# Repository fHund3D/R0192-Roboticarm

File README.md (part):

# Roboticarm-R0192

Der **R0192** ist ein 6-Achsen-Roboterarm, der auf einem hybriden System aus SteadyWin- und RobStride-Aktuatoren basiert. Dieses Repository enthält das vollständige ROS 2 Jazzy-Ökosystem für die CAN-Bus-Kommunikation, die Hardware-Abstraktion, die Bahnplanung via MoveIt 2 sowie ein Arduino-basiertes Hall-Sensor-Homing.

Die gesamte Steuerungslogik (MoveIt 2, ros2_control, CAN-Treiber) läuft auf einem **Raspberry Pi 5**. Eine zentrale **Betriebszustands-Maschine** (`robot_state_manager`) koordiniert Motor-Enable, Jogging, MoveIt-Ausführung, Homing und Notaus als sich gegenseitig ausschließende Zustände. Bedient wird der Arm über ein **RViz-Jog-Panel**, das gezielt zu einem Teach-Pendant-Ersatz ausgebaut wird (später ggf. durch ein echtes Hardware-Teach-Pendant ersetzbar); ein **Web-Interface** (`r0192_remote`) bleibt eine optionale Zukunftsoption. Foxglove Studio spielt nur eine kleine Rolle zum Debuggen. **Alle sechs Aktuatoren sind inzwischen beschafft und montagebereit**; softwareseitig sind die GDS68- und RS05-Antriebsstränge an je einer Achse verifiziert, die Inbetriebnahme der übrigen Achsen läuft.

---

## 🚀 Projekt-Roadmap

### Software (ROS 2 & OS)
- [x] OS-Setup: Ubuntu 24.04 & ROS 2 Jazzy Installation
- [x] Workspace & Paketstruktur initialisiert
- [x] Treiber-Integration: SteadyWin GDS68 (Achse 1–3)
- [x] Treiber-Integration: RobStride RS05 (Achse 4–6)
- [x] CAN-Kommunikation & Hardware Interface (ros2_control, 100 Hz, Closed-Loop)
- [x] URDF/XACRO Modellierung inkl. 3D-Visualisierung & Kollisionsgeometrien
- [x] MoveIt 2 Integration — Bahnplanung & Trajektorienausführung auf Achsen 1 + 4 verifiziert
- [x] Encoder-Homing beim Start (Hardware Interface setzt internen Nullpunkt)
- [x] `foxglove_bridge` in Bringup integriert (Debug-Tool, Port 8765, `use_foxglove:=true`)
- [x] **Homing-Sequenz** mit TLE4905L Hall-Sensoren — Arduino-Firmware (Achse 1) + ROS-Service `/homing` in `r0192_hardware` eingebettet; zweiseitiger Kantenanlauf (Kante A → Überfahren → Kante B → Mitte) implementiert
- [x] **RViz Jog-Panel / Teach-Pendant** (`r0192_rviz_plugins`) über MoveIt Servo: 3 Modi (Joints / Cartesian / Tool), Speed-Slider, Press-and-Hold
- [x] **Zentrale Zustandsmaschine** (`robot_state_manager` + `r0192_interfaces`): 5 exklusive Zustände DISABLED / HOLD / JOG / MOVEIT / HOMING via `/set_robot_state` + `/robot_state`
- [x] **Notaus** (`/e_stop`) — erzwingt DISABLED aus jedem Zustand, latchender Treiber-Torque-Cut (GDS68 `Estop()`, RS05 stop) + Treiber-Reset (`/robot_reset` → `Clear_Errors`) zur Wiederinbetriebnahme
- [x] **Programm-System** (`r0192_program_executor`) — industrielle Trennung Engineering (YAML in VS Code, JSON-Schema-Validierung) ↔ Operations (RViz-Run-Panel „R0192 Program"). Action `/execute_program`, KRL/Pilz-Steps `ptp`/`lin`/`circ` (+ Legacy `move_j`/`move_l`/`wait`), Stop-at-each-point **und** Pilz-Blend-Modus mit `c_dis`, Pause/Resume/Speed-Override, Punkt-Teach. Ersetzt für die Programmierung das ursprünglich geplante Web-Interface
- [ ] **Aktuell: Hardware-Test Homing** — Arduino + Magnet an Achse 1 anschließen und end-to-end validieren
- [ ] **Aktuell: RViz-Jog-Panel zum Teach-Pendant ausbauen** — bedienerfreundlich möglichst nah an ein echtes Teach-Pendant (später ggf. durch ein Hardware-Pendant ersetzbar); ein Web-Interface (`r0192_remote`) bleibt optionale Zukunftsoption
- [ ] **Hardware-Notaus über Schütz/Relay** — schaltet die 48-V-Versorgung hart ab (zusätzlich zum latchenden Treiber-Torque-Cut); laufenden Homing-Sweep abbrechen
- [ ] Echtzeit-Optimierung (RT-Kernel & CPU-Shielding auf RPi 5)

#### Projektstruktur

```
roboticarm_r0192_ws/
├── src/
│   ├── r0192_bringup/         # Bringup Sequenz (real + simuliert)
│   ├── r0192_canbus/          # CAN-Bus Treiber: GDS68, RS05, CanCommunication
│   ├── r0192_controller/      # JTC-Konfiguration, manueller Slider-Node
│   ├── r0192_description/     # URDF/XACRO, STL-Meshes, RViz-Konfiguration
│   ├── r0192_interfaces/      # Custom msgs/srvs: RobotState, SetRobotState
│   ├── r0192_hardware/        # ros2_control HW-Interface + robot_state_manager
│   ├── r0192_moveit/          # MoveIt 2: SRDF, Kinematik, Planung, Servo, Launch
│   ├── r0192_rviz_plugins/    # RViz Jog-Panel / Teach-Pendant (Operator-Panel)
│   └── r0192_remote/          # (Geplant) Web-Interface als Operator-Pendant
├── doku/                      # Datenblätter & Treiber-Dokumentation
├── build/                     # Build-Artefakte (ignoriert)
├── install/                   # Install-Artefakte (ignoriert)
└── log/                       # Logs (ignoriert)
```

#### System-Architektur

```
RViz Jog-Panel  /  Web-Interface (geplant)        Debug-Tools (optional)
  │  /set_robot_state, /e_stop                     RViz  ◄──  ROS-Topics
  │  /robot_state (latched)                        Foxglove ◄─ foxglove_bridge (:8765)
  ▼
robot_state_manager  (zentrale Zustandsmaschine)
  │  koordiniert: /robot_enable, switch_controller, pause_servo, /homing
  ├──────────────► MoveIt 2 + Servo
  │                     │
  ▼                     ▼
ros2_control (100 Hz, Closed-Loop)  ──►  arm_controller / gripper_controller
                 │
         R0192SystemHardware
          ├─ /robot_enable Service (Motor-Torque an/aus)
          ├─ /homing Service (eingebettet, HomingController)
                 │
    ┌────────────┴────────────┐
GDS68Driver              RS05Driver
(Achsen 1–3)             (Achsen 4–6)
    └────────────┬────────────┘
             SocketCAN (can0, 1 Mbit/s)
             MKS CANable Pro → Motoren
                 │
    Arduino Uno R3 (je 1 pro Achse)
    TLE4905L Hall-Sensor + MCP2515
    Homing-Node (CAN-ID 0x100, Codes in Data[0]: CMD_ARM/DETECTED/ERROR)
```

#### Betriebszustände (Robot State Manager)

Der `robot_state_manager` ist die *Single Source of Truth* für den Betriebszustand. Vorher war der Zustand implizit über drei verstreute Flags verteilt (`motors_enabled_`, Homing-aktiv, Servo-Pause) — jetzt 5 exklusive Zustände mit erzwungenen Übergängen:

| Zustand | Motor-Torque | `arm_controller` | Servo | Bedeutung |
| :--- | :--- | :--- | :--- | :--- |
| `DISABLED` | aus | inaktiv | pausiert | Idle, drehmomentfrei (Startzustand) |
| `HOLD` | an | inaktiv | pausiert | Servos an, Hardware hält letzte Soll-Pos |
| `JOG` | an | aktiv | aktiv | Teach-Pendant über MoveIt Servo |
| `MOVEIT` | an | aktiv | pausiert | move_group darf Trajektorien ausführen |
| `HOMING` | an | (Homing managed) | pausiert | Homing-Sequenz läuft |

Übergänge: `DISABLED ⇄ HOLD`, und aus `HOLD` heraus `→ JOG / MOVEIT / HOMING` (jeweils zurück nach `HOLD`). `/e_stop` erzwingt `DISABLED` aus **jedem** Zustand und kappt das Drehmoment **auf Treiber-Ebene** (GDS68 `Estop()` 0x002 latchend, RS05 stop). Die Treiber sind danach bewusst in einem Fehlerzustand „gefangen" — `/robot_reset` (→ Hardware `Clear_Errors` / RS05-Fault-Clear) löst das, erst dann ist `DISABLED→HOLD` wieder erlaubt. Clients (RViz-Panel, künftiges Web-Interface) steuern ausschließlich über `/set_robot_state` und spiegeln das latched `/robot_state` — nie direkt `/robot_enable` / `/homing` / `pause_servo`.

### Hardware & Mechanik
- [x] Kinematische Auslegung & Motorauswahl
- [x] Grobes mechanisches Design (CAD)
- [x] Beschaffung **aller 6 Aktuatoren** abgeschlossen (4× SteadyWin GIM @ GDS68, 2× RobStride RS05)
- [ ] Detail-Konstruktion & Optimierung der Steifigkeit
- [ ] Full-Scale 3D-Druck Prototyping (PLA/PETG)
- [ ] **Geplant:** Substitution kritischer Strukturbauteile durch CNC-Aluminium
- [ ] **Steuerungs- & Versorgungsschrank** (Item-/Profil-5-Alu, 20×20) — separates Gehäuse für beide Netzteile, ODrive Regen Clamp & Raspberry Pi als externe Steuerung/Stromversorgung des Arms

### Elektronik (PCB Design)
- [x] Schaltungskonzept & Leistungsplanung
- [x] Design Daisy-Chain PCB (PCB 2) - *Draft*
- [ ] Design Breakout-Board (PCB 1) - *Main Power Distribution*
- [ ] Not-Aus-Schütz 48 V aufbauen (Konzept steht: [`doku/estop_konzept.md`](doku/estop_konzept.md))
- [ ] PCB-Fertigung (PCBWay) & Bestückung
- [ ] Systemintegration & EMV-Tests

---

## 🛠 Technische Spezifikationen

### Achskonfiguration

> **Alle sechs Aktuatoren sind beschafft.** Achsen 1–4 nutzen SteadyWin-GIM-Motoren am **GDS68**-Treiber (11-bit-Standard-CAN), Achsen 5–6 RobStride **RS05** (29-bit-Extended-CAN). Achse 4 wurde von RS05 auf einen **GIM6010-8** umgestellt (24 V, ohne Bremse — der zuerst beschaffte Motor); Achsen 1–3 sind die 48-V-Varianten **mit Bremse** — sie legen den größten Weg zurück und tragen die größte Last; die Bremse hält sie stromlos in Position und verhindert ein Zusammenfallen des Arms ohne Strom. Achsen 5–6 sind RS05 @ 48 V.

| Achse | Motor | Treiber | Spannung / Bremse | Besonderheit | Lagerung | Status |
| :--- | :--- | :--- | :--- | :--- | :--- | :--- |
| **Axis 1** | [GIM6010-8](https://openelab.de/products/steadywin-gim6010-8-planetengetriebemotor?variant=54009308873041) | GDS68 | 48 V · mit Bremse | High Torque Base | [Kreuzlager RU66](https://de.aliexpress.com/item/1005008094900625.html) | ✅ Vorhanden |
| **Axis 2** | [GIM8108-8](https://openelab.de/products/steadywin-gim8108-8?variant=54041139609937) | GDS68 | 48 V · mit Bremse | Hauptausleger | [Kreuzlager RU42](https://de.aliexpress.com/item/1005008094900625.html) | ✅ Vorhanden |
| **Axis 3** | [GIM6010-8](https://openelab.de/products/steadywin-gim6010-8-planetengetriebemotor?variant=54009308873041) | GDS68 | 48 V · mit Bremse | Ellenbogen | - | ✅ Vorhanden |
| **Axis 4** | [GIM6010-8](https://openelab.de/products/steadywin-gim6010-8-planetengetriebemotor?variant=54009308873041) | GDS68 | 24 V · ohne Bremse | Zuerst beschaffter Motor (ersetzt RS05) | - | ✅ Vorhanden |
| **Axis 5** | [RS05](https://openelab.de/products/robstride05-qdd-55nm-joint-motor-robotik?variant=52331724931409) | Intern | 48 V | 1:2 Übersetzung (Torque) | [Kreuzlager RU28](https://de.aliexpress.com/item/1005008094900625.html) | ✅ Vorhanden |
| **Axis 6** | [RS05](https://openelab.de/products/robstride05-qdd-55nm-joint-motor-robotik?variant=52331724931409) | Intern | 48 V | Endeffektor Rotation | - | ✅ Vorhanden |

> **Code-Hinweis:** Achse 4 ist jetzt ein GIM6010-8 am **GDS68**-Treiber (11-bit-Standard-CAN) statt bisher RS05 (29-bit-Extended-CAN). Im Hardware-Interface/Treiber-Mapping ist Achse 4 noch der RS05-Zuordnung zugewiesen — die Code-Migration steht aus.

### Elektronik & Steuerung
* **Recheneinheit:** Raspberry Pi 5 (8GB RAM)
* **CAN-Interface:** MKS CANable Pro (Isoliert), SocketCAN (`can0`)
* **CAN-Bitrate:** 1 Mbit/s (info: 500 kbit/s GDS68 Werkseinstellung)
* **Energieversorgung:**
    * Bus-Spannung: 48 V — MeanWell LRS-600N2-48
    * Logik-Spannung: 5 V — MeanWell LRS-50
    * Steuerspannung Not-Aus-Kette: 24 V — separates Netzteil, nur für Schütz- und Relaisspulen
    * Regen-/Bremsenergie: [ODrive Regen Clamp](https://eu.odriverobotics.com/shop/odrive-regen-clamp) am 48-V-Bus — verhindert Überspannung beim Abbremsen/Rückspeisen der Motoren (2 Ohm und 50W Widerstand)
* **Steuerungs- & Versorgungsschrank:** separates Gehäuse aus Item-/Profil-5-Aluprofilen (20×20) — nimmt beide Netzteile, die Regen Clamp und den Raspberry Pi auf und bildet die externe Steuerung & Stromversorgung des Arms
* **Umbilical-Steckverbindung (Schrank ↔ Arm):** Heavy-Duty-Rechteckstecker im **Han-E-Format, 24-polig** (Typ HDC-HE-024, Harting-Han-24E-kompatibel) — 16 A/Kontakt, 500 V, 0,5–6 mm² Schraubanschluss, Metallgehäuse (Schirm-/PE-Anbindung), IP65. Führt 48 V, 5 V, Bremse (Achsen 1–3) und CAN in einem Stecker; CAN-Trio in einer Ecke mit GND-Guard, Kabelschirm aufs Metallgehäuse
* **Homing-Sensorik:** TLE4905L Hall-Effekt-Sensoren, je ein Node pro Achse — Prototyp Achse 1 mit Arduino Uno R3 + MCP2515, Zielhardware **XIAO-ESP32-S3 (natives TWAI)** auf der Daisy-Chain-Platine
* **Haltebremsen:** SteadyWin STW-S035 (24 V / 0,64 A, stromlos geschlossen), **PWM-gechoppt aus 48 V** über eine Low-Side-Endstufe pro Achse (Anzug 100 % Duty ~150 ms, Halten ~10,4 % Duty ≈ 0,7 W). **Am Arm liegt kein 24-V-Netz** — das 24-V-Netzteil im Schrank versorgt nur die Not-Aus-Kette.
* **Not-Aus (Hardware, geplant):** DC-Schütz in der 48-V-Schiene mit Selbsthaltung und Wiederanlaufschutz, Steuerkette über ein eigenes 24-V-Netzteil. Konzept: [`doku/estop_konzept.md`](doku/estop_konzept.md)
* **Schnittstellen (Platine):** WAGO 2601-3104 (Power-Durchschleife + Motorabzweig), Phoenix PTSM 0,5/3-2,5-V-THR (CAN), JST PH B3B-PH-K (Hall + Bremse) — Details in [`PCB/pcb_daisy_chain.md`](PCB/pcb_daisy_chain.md)

#### Verkabelung

Auslegung mit dem **200%-Kurzzeit-Peak** der Netzteile (48 V: 12,5 A Dauer → ~25 A Peak). Cu hat thermische Trägheit — der Peak ist eher für die **Schutzorgane** (träge Sicherung) relevant als für den Querschnitt.

| Kreis | Querschnitt | Kabeltyp |
| :--- | :--- | :--- |
| **48 V Trunk** (Box → Arm-Basis) | 2,5 mm² (≈14 AWG) | Silikon-Litze, feindrähtig (Klasse 5/6) |
| 48 V → Motor (Abzweig) | 1,0–1,5 mm² | Silikon-Litze (Achse 2 / GIM8108 → 1,5 mm²) |
| **5 V Logik** | 1,0 mm² (≈18 AWG) | Silikon-Litze (Querschnitt wegen Spannungsabfall, nicht Strom) |
| Bremse (Achsen 1–3, falls separat) | 0,5–0,75 mm² | Silikon-Litze (wenig Strom, kurzer Inrush) |
| **CAN** | 2×2×0,34 mm² | geschirmte, verdrillte CAN-Busleitung, **120 Ω** |

**Bewegung an den Gelenken** ist entscheidend für die Lebensdauer:

- **Drehachsen 1, 4, 6** (tordieren) → **torsionsfähige Roboterleitung** (z. B. Lapp ÖLFLEX ROBOT, igus chainflex), keine reine Biege-Schleppkettenleitung.
- **Biegeachsen 2, 3, 5** → Schleppketten-/Dauerbiege-Leitung genügt.
- Innerhalb eines Glieds (unbewegt) → einfache Silikon-Litze.

**CAN-Hinweise:** dediziertes 120-Ω-Buskabel (nicht zwei Adern aus dem Powerkabel), `CAN_GND` als Referenz mitführen, Schirm **steuerboxseitig** auf PE/Metallgehäuse (Han-E-Stecker); 48 V und CAN nicht ungeschirmt im selben Mantel bündeln.

**Konkrete Kabelauswahl (igus chainflex, Stand 2026-07):** Für das Hobby-Budget bewusst pragmatisch gewählt — eine Power-Kabelsorte für alles, günstige PVC-Busleitung statt teurer Torsionsvariante.

| Verwendung | igus Art-Nr. | Aufbau | Notiz |
| :--- | :--- | :--- | :--- |
| Power-Durchschleife 48 V + 5 V (Daisy-Chain) | **CF77.UL.15.04.D** | 4G1,5, PUR | Zwei getrennte Paare: 48 V / 48 V-GND + 5 V / 5 V-GND. GN-YE-Ader als vollwertiger Rückleiter nutzen (zulässig, da einheitliches GND-Netz). Kein gemeinsamer GND-Rückleiter — sonst summiert sich der Rückstrom auf dem Basissegment über 1,5 mm². |
| CAN-Bus-Durchschleife | **CFBUS.PVC.021** | (2×0,5)C, geschirmt | Biege-/Energieketten-Leitung (PVC), **keine Torsionsleitung**. Torsions-Upgrade (CFROBOT8.PLUS.022, CAN, torsionsfest) bewusst aus Kostengründen zurückgestellt — an rotierenden Gelenken später ggf. nur das kurze Gelenkstück tauschen. |
| PCB → Motor (Abzweig) | **CF77.UL.15.04.D** | 4G1,5, PUR | Kurz/statisch; nur 48 V + GND genutzt (CAN separat über die Busleitung). Bei hohem Motor-Peak (GIM8108 ~22 A) je 2 Adern parallel für 48 V bzw. GND → ~3 mm². Für Achse 1 (GIM6010 ~18 A) / Achse 4 (RS05 ~11 A) genügt eine Einzelader. |

> **Bezug:** igus liefert auch an Privatkunden über den Online-Shop, ab 1 m Länge ohne Mindestbestellwert. Shop-Preise sind netto — zzgl. MwSt., Kupferzuschlag und Versand. CFBUS.PVC.021 ~3,35 €/m, CF77.UL.15.04.D ~3,52 €/m (zzgl. Zuschläge).

**Materialkosten (grob, DE-Retail):** Silikon-Litze für Power/5V/Bremse ist günstig (~30–50 €), CAN-Leitung ~15–25 €. Kostentreiber ist die Torsions-/Roboterleitung an den Drehachsen. Gesamt: **~60–100 €** maker-pragmatisch (Silikon-Litze überall), **~120–220 €** mit Marken-Roboterleitung an den Gelenken; dazu Kleinkram (Aderendhülsen, Schrumpfschlauch, Gewebeschlauch) ~25–50 €.

> **Hinweis zu URDF-Werten:** Alle Gelenkgrenzen, Trägheitsmomente und Schwerpunkte in der URDF sind derzeit Platzhalter und werden nach Abschluss des CAD-Designs mit realen Werten befüllt.

---

---

## Quickstart (RPi)

```bash
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
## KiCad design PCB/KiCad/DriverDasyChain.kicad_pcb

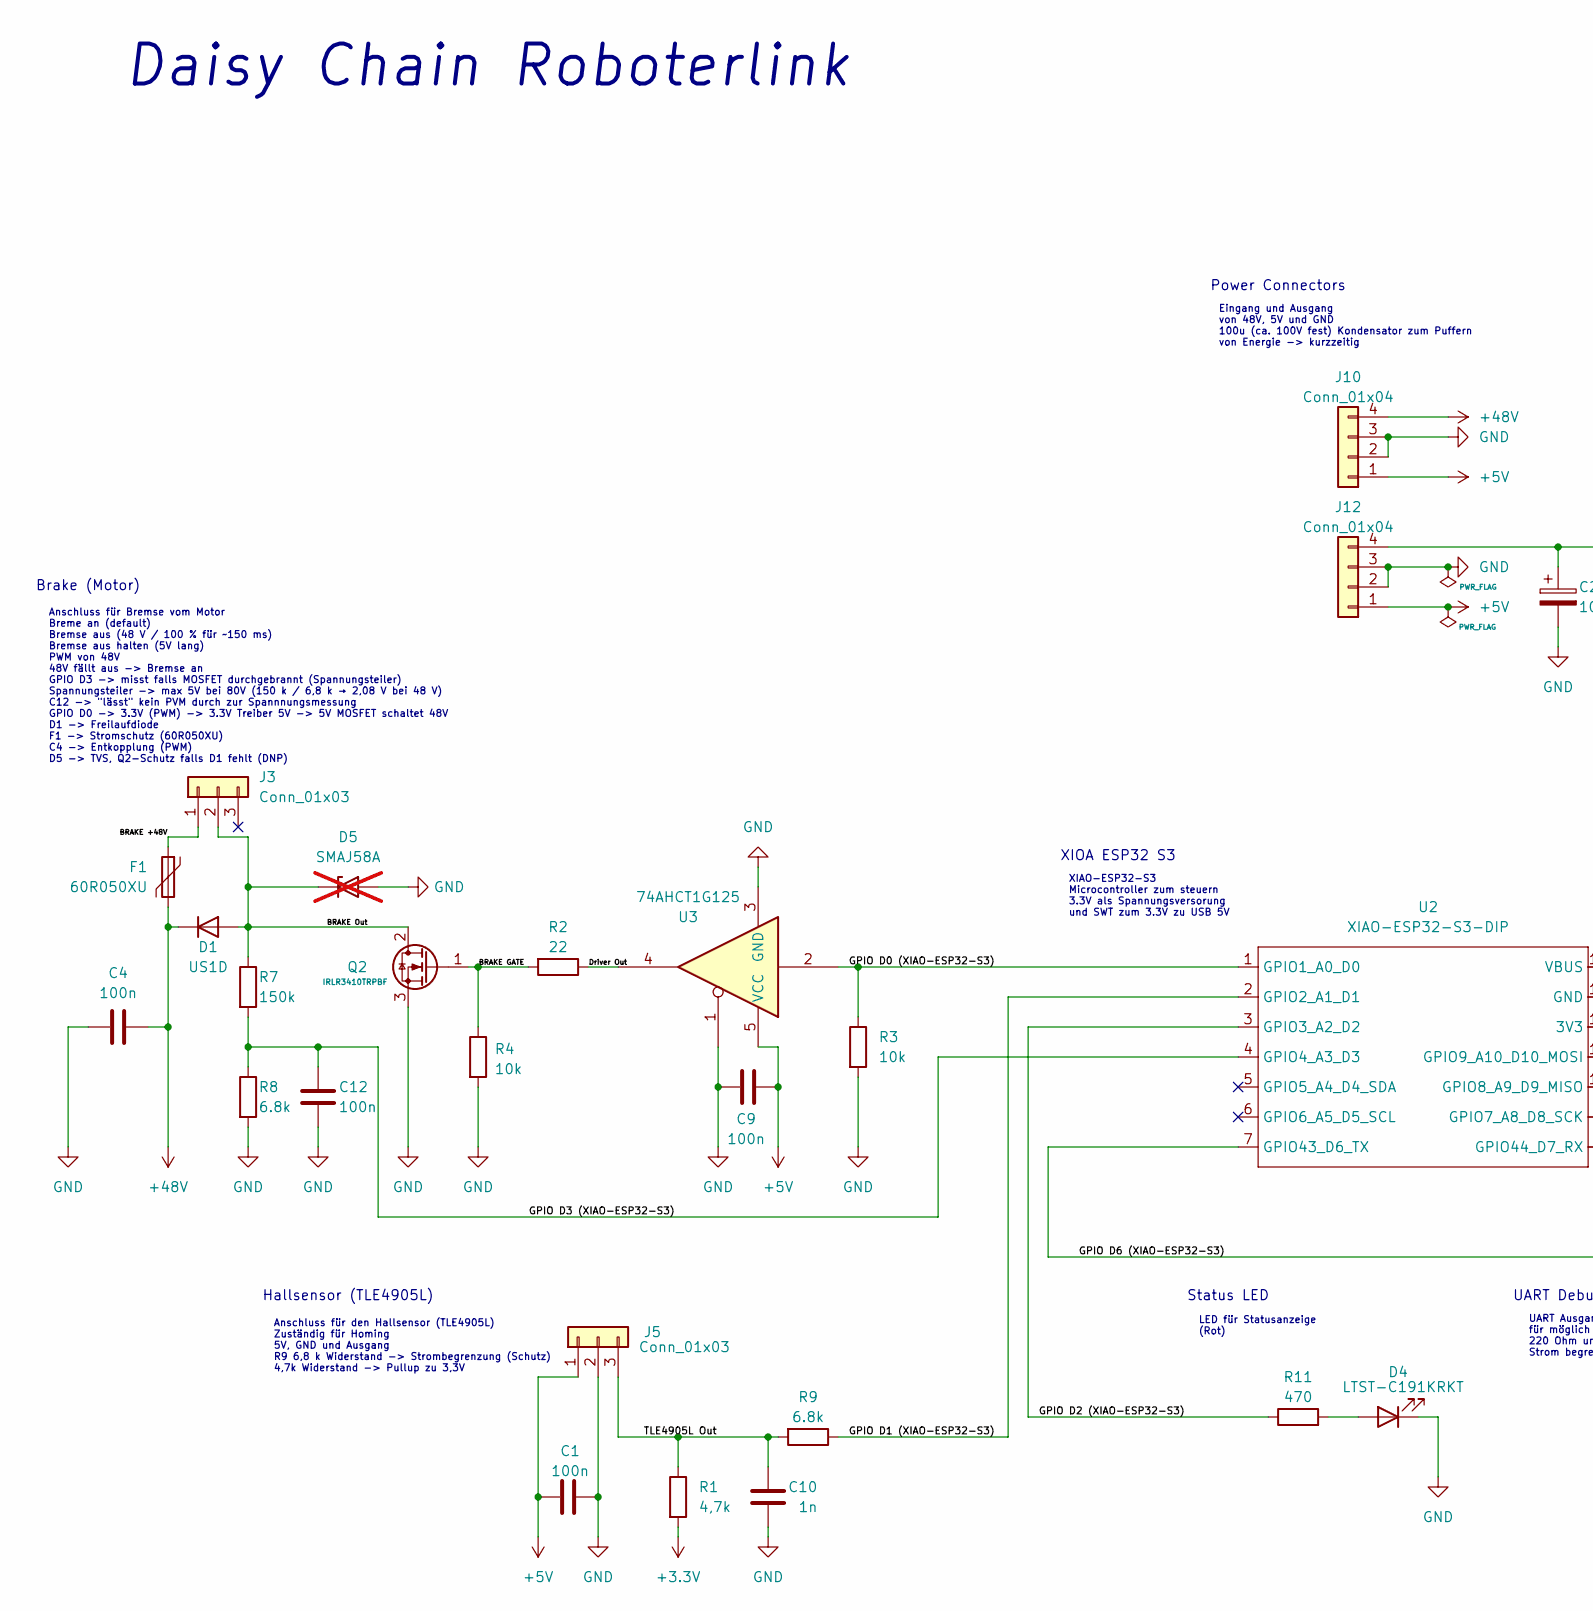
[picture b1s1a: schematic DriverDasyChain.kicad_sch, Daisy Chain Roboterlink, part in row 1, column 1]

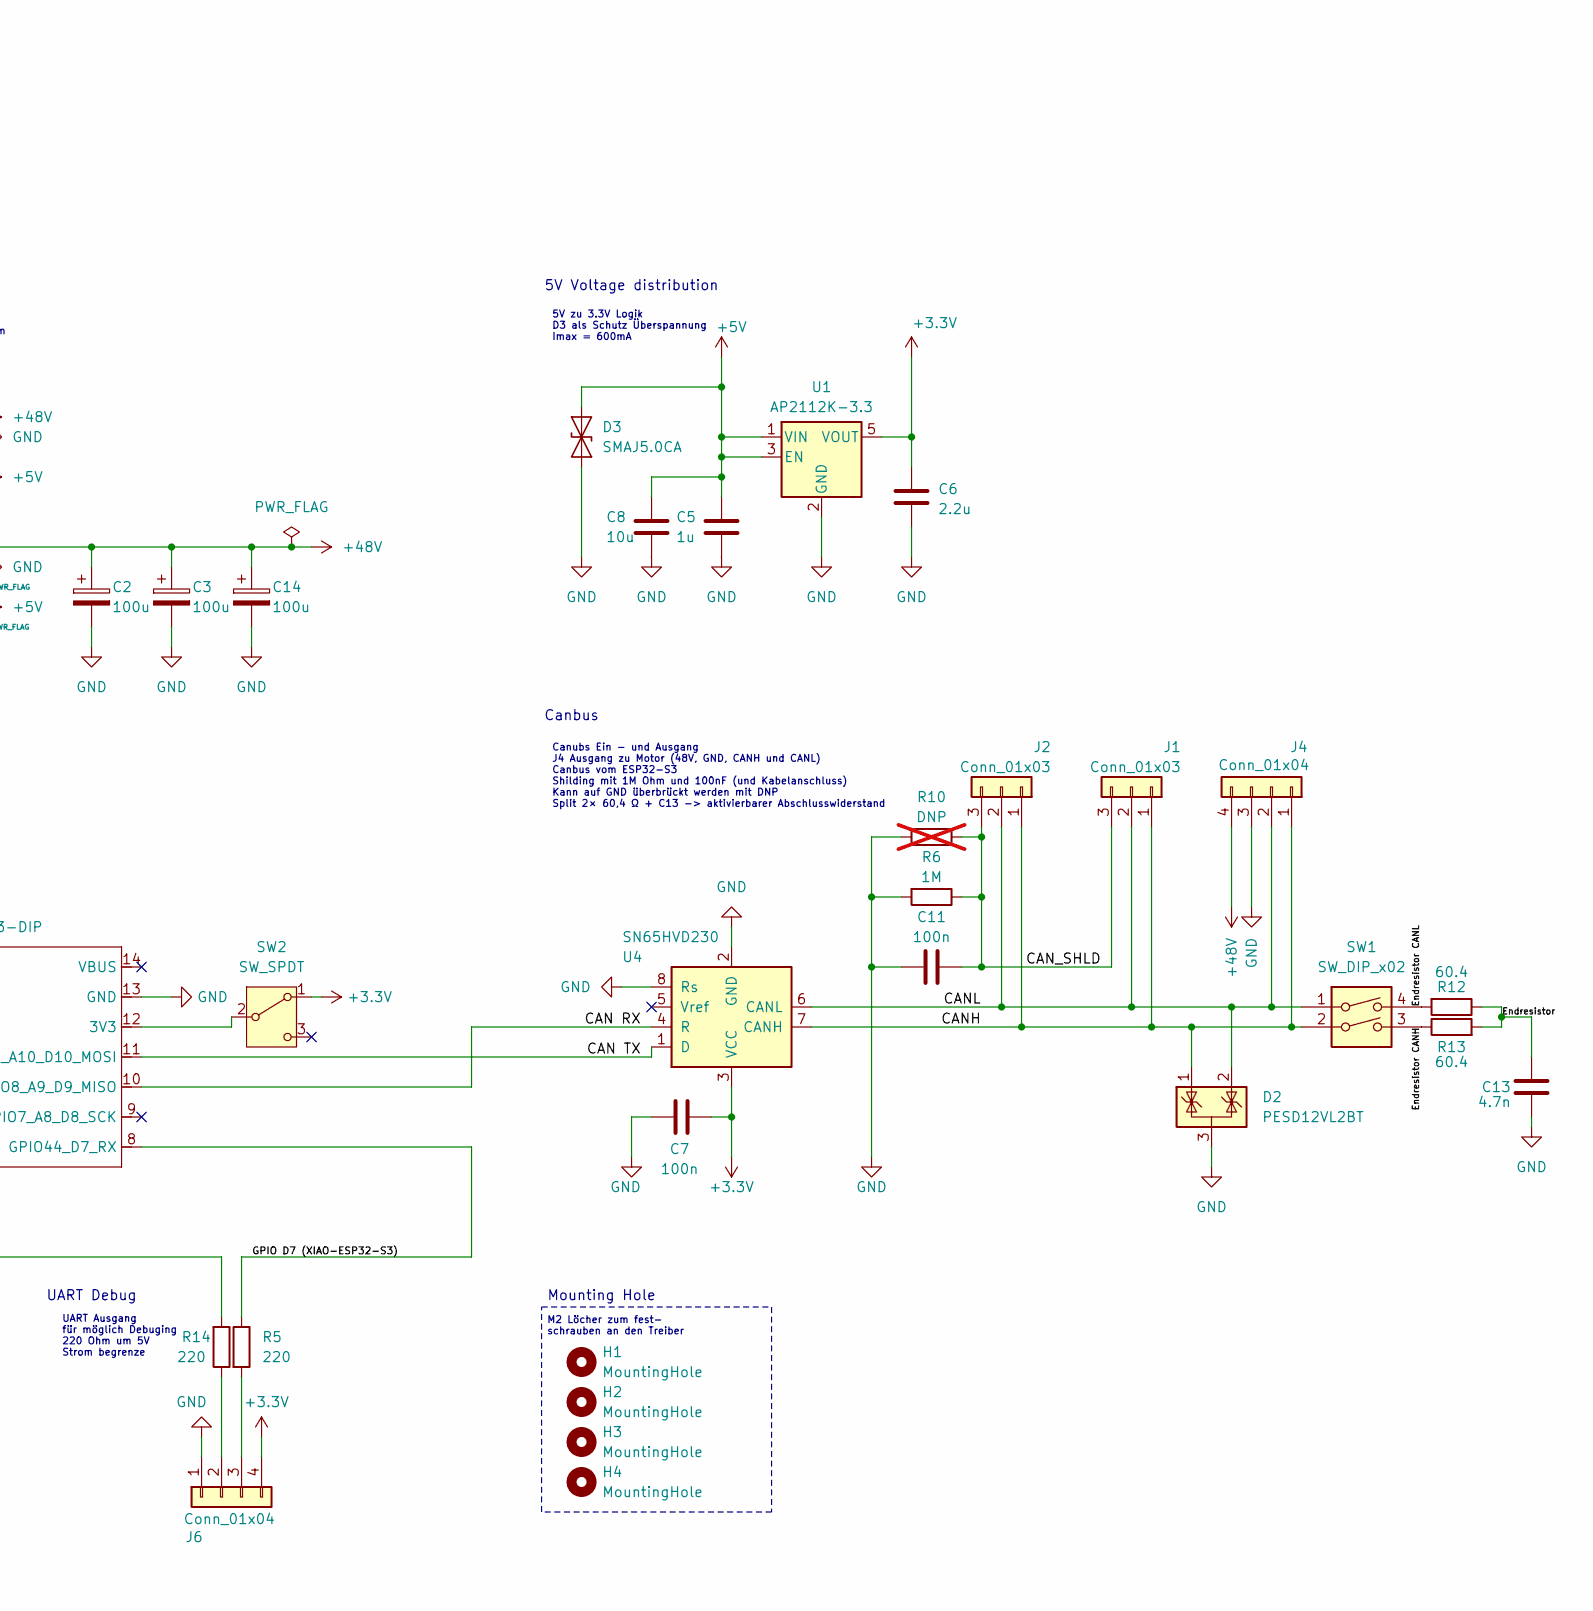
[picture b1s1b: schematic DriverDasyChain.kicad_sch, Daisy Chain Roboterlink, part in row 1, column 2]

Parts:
C1, C7, C9, C11, C12: 100n; C_0603_1608Metric_Pad1.08x0.95mm_HandSolder
C2, C3, C14: 100u; CP_Radial_D10.0mm_P5.00mm
C4: 100n; C_0805_2012Metric_Pad1.18x1.45mm_HandSolder
C5: 1u; C_0603_1608Metric_Pad1.08x0.95mm_HandSolder
C6: 2.2u; C_0603_1608Metric_Pad1.08x0.95mm_HandSolder
C8: 10u; C_0805_2012Metric_Pad1.18x1.45mm_HandSolder
C10: 1n; C_0603_1608Metric_Pad1.08x0.95mm_HandSolder
C13: 4.7n; C_0603_1608Metric_Pad1.08x0.95mm_HandSolder
D1: US1D; D_SMA
D2: PESD12VL2BT; SOT-23
D3: SMAJ5.0CA; D_SMA
D4: LTST-C191KRKT; LED_0603_1608Metric_Pad1.05x0.95mm_HandSolder
D5: SMAJ58A; D_SMA; not fitted
F1: 60R050XU; Fuse_Littelfuse_60R050XU
H1, H2, H3, H4: MountingHole; MountingHole_2.2mm_M2_Pad_TopBottom
J1, J2: Conn_01x03; TerminalBlock_Phoenix_PTSM-0,5-3-2.5-V-THR_1x03_P2.50mm_Ver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
J3, J5: Conn_01x03; JST_PH_B3B-PH-K_1x03_P2.00mm_Vertical
J4, J10, J12: Conn_01x04; TerminalBlock_WAGO_2601-3104_1x04_P3.50mm_Vertical
J6: Conn_01x04; PinHeader_1x04_P2.54mm_Vertical
Q2: IRLR3410TRPBF; TO-252-2
R1: 4,7k; R_0603_1608Metric_Pad0.98x0.95mm_HandSolder
R2: 22; R_0603_1608Metric_Pad0.98x0.95mm_HandSolder
R3, R4: 10k; R_0603_1608Metric_Pad0.98x0.95mm_HandSolder
R5, R14: 220; R_0603_1608Metric_Pad0.98x0.95mm_HandSolder
R6: 1M; R_0603_1608Metric_Pad0.98x0.95mm_HandSolder
R7: 150k; R_0603_1608Metric_Pad0.98x0.95mm_HandSolder
R8, R9: 6.8k; R_0603_1608Metric_Pad0.98x0.95mm_HandSolder
R10: DNP; R_0603_1608Metric_Pad0.98x0.95mm_HandSolder; not fitted
R11: 470; R_0603_1608Metric_Pad0.98x0.95mm_HandSolder
R12, R13: 60.4; R_0603_1608Metric_Pad0.98x0.95mm_HandSolder
SW1: SW_DIP_x02; SW_DIP_SPSTx02_Slide_6.7x6.64mm_W6.73mm_P2.54mm_LowProfile_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
SW2: SW_SPDT; SW_SPDT_PCM12
U1: AP2112K-3.3; SOT-23-5
U2: XIAO-ESP32-S3-DIP
U3: 74AHCT1G125; SOT-23-5
U4: SN65HVD230; SOIC-8_3.9x4.9mm_P1.27mm

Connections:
+3.3V: C6.1, C7.2, J6.4, R1.2, SW2.1 (A), U1.5 (VOUT), U4.3 (VCC)
+5V: C1.1, C5.2, C8.2, C9.2, D3.2 (A2), J5.1, J10.1, J12.1, U1.1 (VIN), U1.3 (EN), U3.5 (VCC)
+48V: C2.1, C3.1, C4.2, C14.1, D1.1 (K), F1.2, J4.4, J10.4, J12.4
/BRAKE +48V: F1.1, J3.1
/BRAKE GATE: Q2.1 (G), R2.2, R4.1
/BRAKE Out: D1.2 (A), D5.1 (A1), J3.2, Q2.2 (D), R7.1
/CAN RX: U2.10 (GPIO8_A9_D9_MISO), U4.4 (R)
/CAN TX: U2.11 (GPIO9_A10_D10_MOSI), U4.1 (D)
/CANH: D2.1 (K), J1.1, J2.1, J4.1, SW1.2, U4.7 (CANH)
/CANL: D2.2 (K), J1.2, J2.2, J4.2, SW1.1, U4.6 (CANL)
/CAN_SHLD: C11.2, J1.3, J2.3, R6.1, R10.2
/Driver Out: R2.1, U3.4
/Endresistor: C13.1, R12.1, R13.2
/Endresistor CANH: R13.1, SW1.3
/Endresistor CANL: R12.2, SW1.4
/GPIO D0 (XIAO-ESP32-S3): R3.1, U2.1 (GPIO1_A0_D0), U3.2
/GPIO D1 (XIAO-ESP32-S3): R9.1, U2.2 (GPIO2_A1_D1)
/GPIO D2 (XIAO-ESP32-S3): R11.1, U2.3 (GPIO3_A2_D2)
/GPIO D3 (XIAO-ESP32-S3): C12.1, R7.2, R8.1, U2.4 (GPIO4_A3_D3)
/GPIO D6 (XIAO-ESP32-S3): R14.2, U2.7 (GPIO43_D6_TX)
/GPIO D7 (XIAO-ESP32-S3): R5.1, U2.8 (GPIO44_D7_RX)
/TLE4905L Out: C10.1, J5.3, R1.1, R9.2
GND: C1.2, C2.2, C3.2, C4.1, C5.1, C6.2, C7.1, C8.1, C9.1, C10.2, C11.1, C12.2, C13.2, C14.2, D2.3 (A), D3.1 (A1), D4.1 (K), D5.2 (A2), J4.3, J5.2, J6.1, J10.2, J10.3, J12.2, J12.3, Q2.3 (S), R3.2, R4.2, R6.2, R8.2, R10.1, U1.2 (GND), U2.13 (GND), U3.1, U3.3 (GND), U4.2 (GND), U4.8 (Rs)
unnamed: D4.2 (A), R11.2
unnamed: J6.2, R14.1
unnamed: J6.3, R5.2
unnamed: SW2.2 (B), U2.12 (3V3)

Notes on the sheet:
XIAO-ESP32-S3 Microcontroller zum steuern 3.3V als Spannungsversorung und SWT zum 3.3V zu USB 5V
Brake (Motor)
5V Voltage distribution
UART Ausgang für möglich Debuging 220 Ohm um 5V Strom begrenze
Canbus
Daisy Chain Roboterlink
Hallsensor (TLE4905L)
Anschluss für Bremse vom Motor Breme an (default) Bremse aus (48 V / 100 % für ~150 ms) Bremse aus halten (5V lang) PWM von 48V 48V fällt aus -> Bremse an GPIO D3 -> misst falls MOSFET durchgebrannt (Spannungsteiler) Spannungsteiler -> max 5V bei 80V (150 k / 6,8 k → 2,08 V bei 48 V) C12 -> "lässt"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
Eingang und Ausgang von 48V, 5V und GND 100u (ca. 100V fest) Kondensator zum Puffern von Energie -> kurzzeitig
Mounting Hole
Status LED
Canubs Ein - und Ausgang J4 Ausgang zu Motor (48V, GND, CANH und CANL) Canbus vom ESP32-S3 Shilding mit 1M Ohm und 100nF (und Kabelanschluss) Kann auf GND überbrückt werden mit DNP Split 2× 60,4 Ω + C13 -> aktivierbarer Abschlusswiderstand
Power Connectors
M2 Löcher zum fest- schrauben an den Treiber
5V zu 3.3V Logik D3 als Schutz Überspannung Imax = 600mA
UART Debug
LED für Statusanzeige (Rot)
XIOA ESP32 S3
Anschluss für den Hallsensor (TLE4905L) Zuständig für Homing 5V, GND und Ausgang R9 6,8 k Widerstand -> Strombegrenzung (Schutz) 4,7k Widerstand -> Pullup zu 3,3V

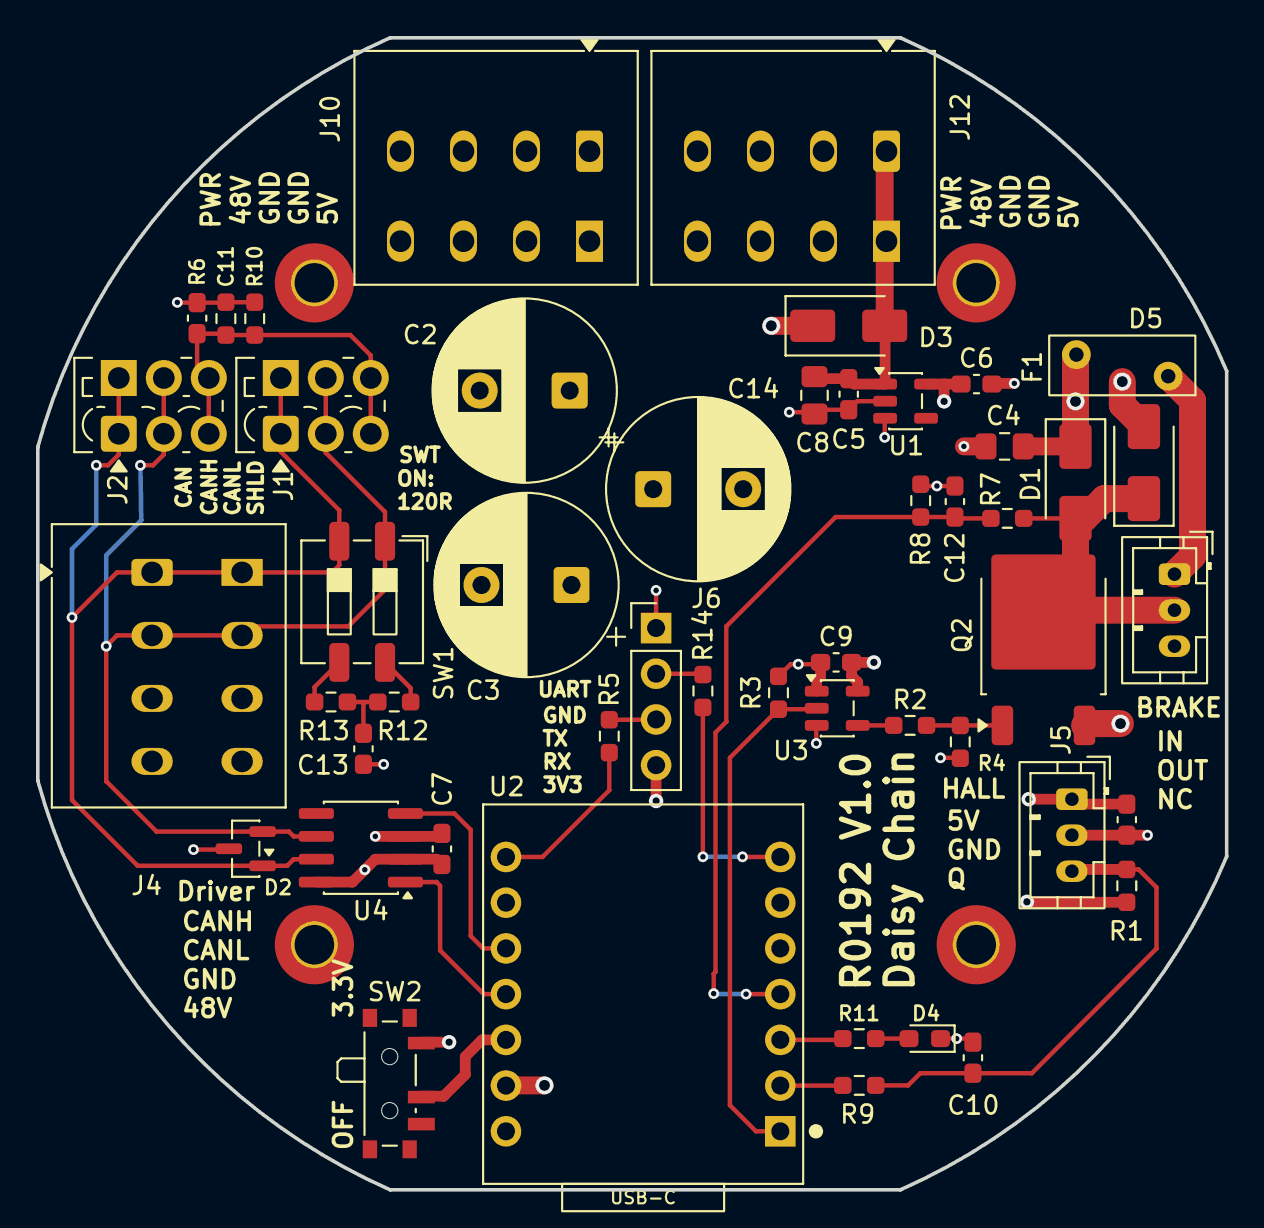
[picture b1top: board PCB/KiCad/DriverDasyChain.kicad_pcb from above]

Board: 4 copper layers, 66.1 x 64.0 mm, 53 parts (0 on the bottom side), 27 nets.

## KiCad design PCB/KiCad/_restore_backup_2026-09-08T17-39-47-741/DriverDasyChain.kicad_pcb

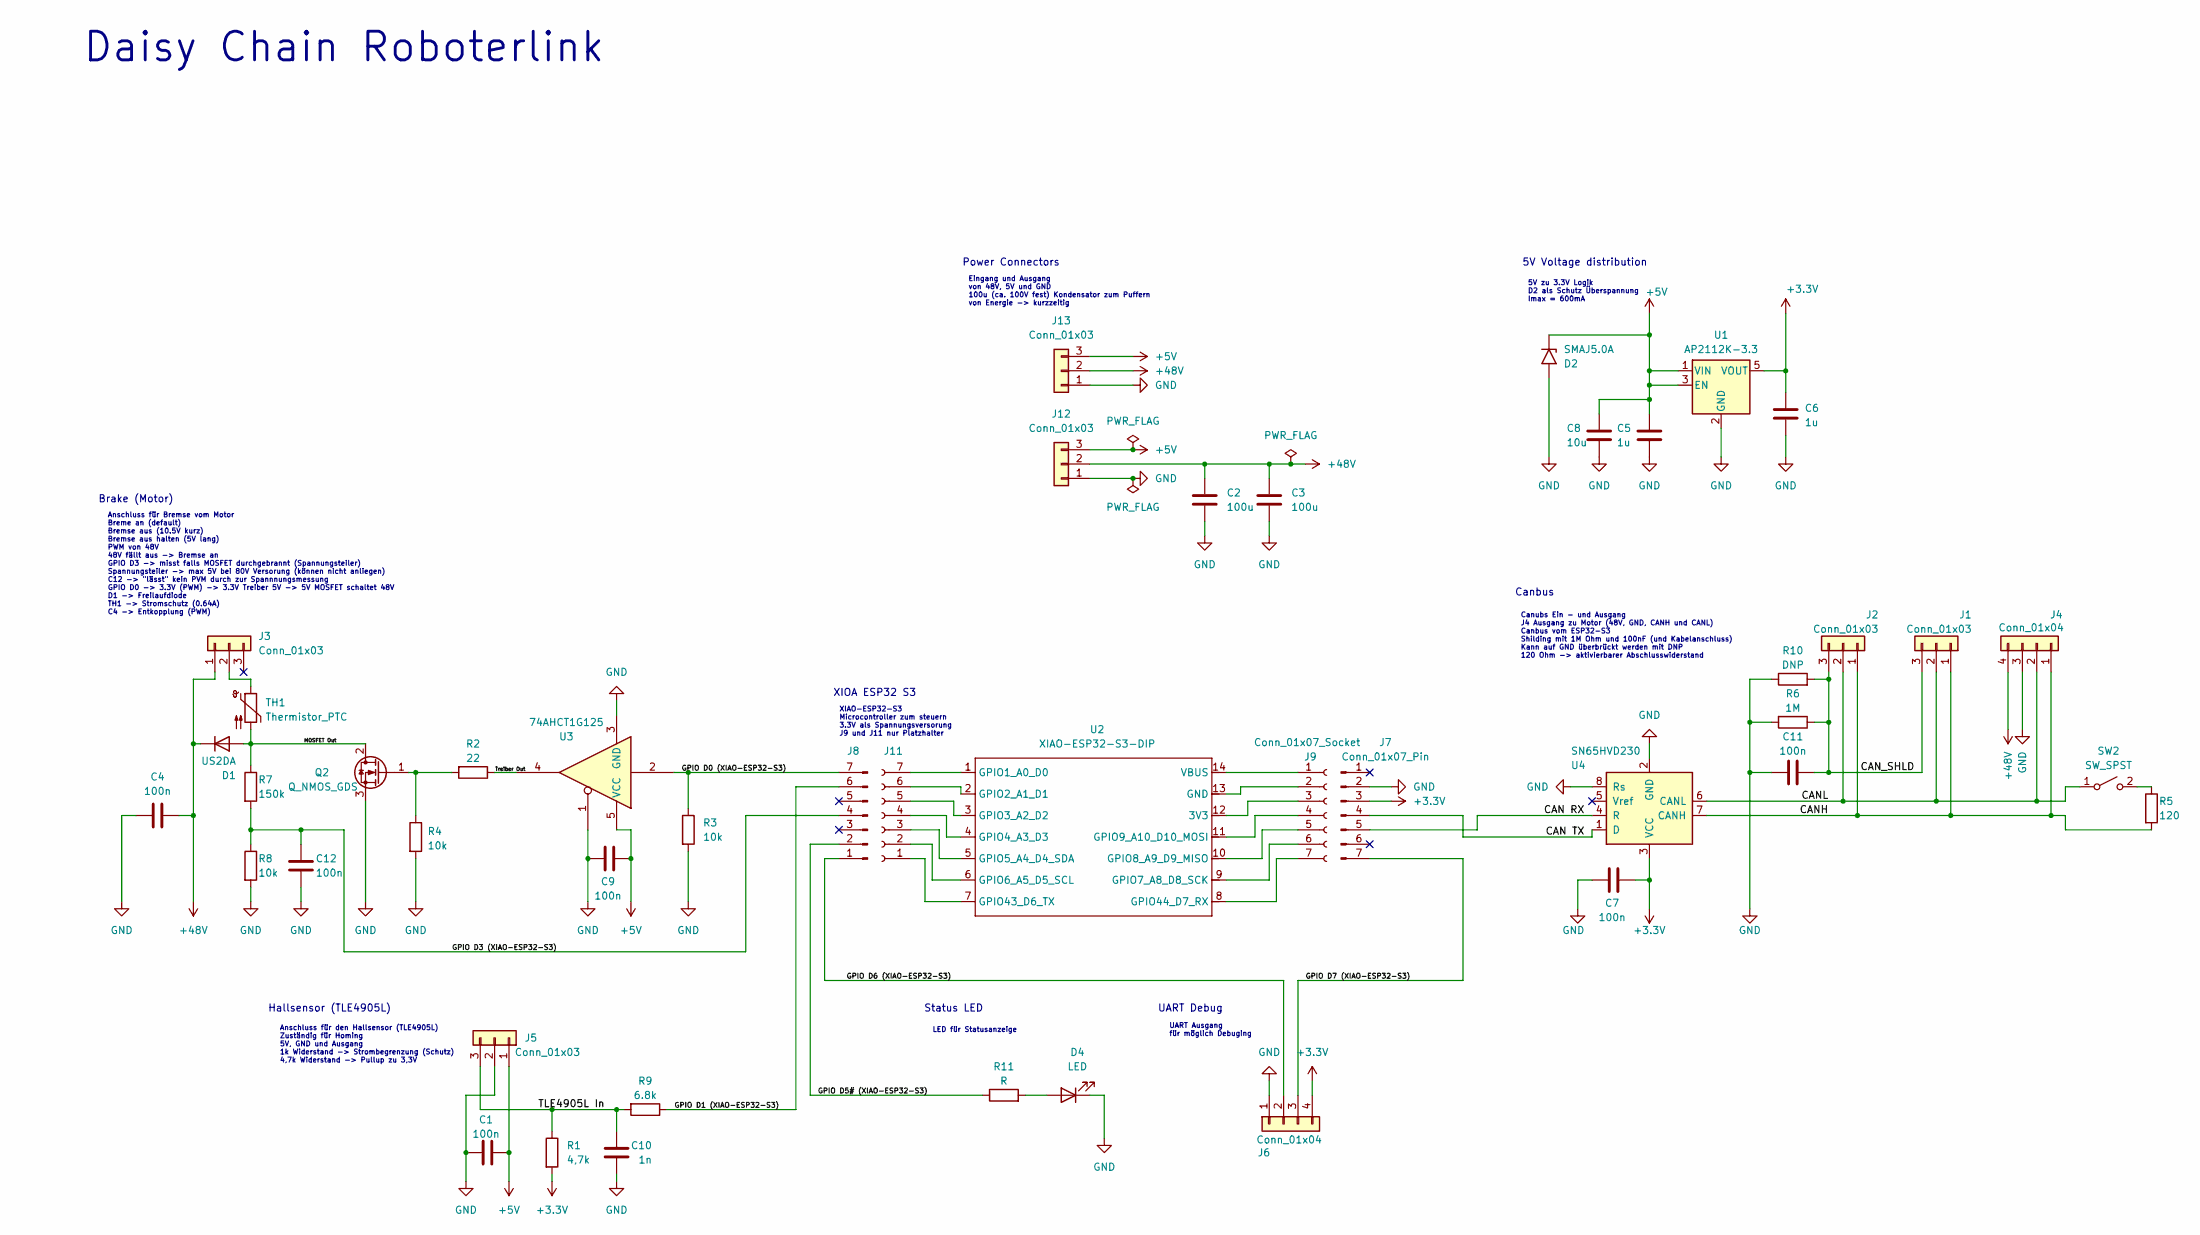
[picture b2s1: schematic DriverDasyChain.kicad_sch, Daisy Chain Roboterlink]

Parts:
C1, C7, C9, C11, C12: 100n; C_0603_1608Metric_Pad1.08x0.95mm_HandSolder
C2, C3: 100u; CP_Radial_D10.0mm_P5.00mm
C4: 100n; C_0805_2012Metric_Pad1.18x1.45mm_HandSolder
C5, C6: 1u; C_0603_1608Metric_Pad1.08x0.95mm_HandSolder
C8: 10u; C_0805_2012Metric_Pad1.18x1.45mm_HandSolder
C10: 1n; C_0603_1608Metric_Pad1.08x0.95mm_HandSolder
D1: US2DA; D_SMA
D2: SMAJ5.0A; D_SMA
D4: LED; LED_0603_1608Metric_Pad1.05x0.95mm_HandSolder
J1, J2: Conn_01x03; TerminalBlock_Phoenix_PTSM-0,5-3-2.5-V-THR_1x03_P2.50mm_Ver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
J3, J5: Conn_01x03; JST_PH_B3B-PH-K_1x03_P2.00mm_Vertical
J4: Conn_01x04; TerminalBlock_WAGO_2601-3104_1x04_P3.50mm_Vertical
J6: Conn_01x04; PinHeader_1x04_P2.54mm_Vertical
J7, J8: Conn_01x07_Pin; PinHeader_1x07_P2.54mm_Vertical
J9, J11: Conn_01x07_Socket
J12, J13: Conn_01x03; TerminalBlock_WAGO_2601-3104_1x04_P3.50mm_Vertical
Q2: Q_NMOS_GDS; TO-252-2
R1: 4,7k; R_0603_1608Metric_Pad0.98x0.95mm_HandSolder
R2: 22; R_0603_1608Metric_Pad0.98x0.95mm_HandSolder
R3, R4, R8: 10k; R_0603_1608Metric_Pad0.98x0.95mm_HandSolder
R5: 120; R_0603_1608Metric_Pad0.98x0.95mm_HandSolder
R6: 1M; R_0603_1608Metric_Pad0.98x0.95mm_HandSolder
R7: 150k; R_0603_1608Metric_Pad0.98x0.95mm_HandSolder
R9: 6.8k; R_0603_1608Metric_Pad0.98x0.95mm_HandSolder
R10: DNP; R_0603_1608Metric_Pad0.98x0.95mm_HandSolder
R11: R; R_0603_1608Metric_Pad0.98x0.95mm_HandSolder
SW2: SW_SPST; SW_DIP_SPSTx01_Slide_Copal_CHS-01A_W5.08mm_P1.27mm_JPin
TH1: Thermistor_PTC
U1: AP2112K-3.3; SOT-23-5
U2: XIAO-ESP32-S3-DIP
U3: 74AHCT1G125; SOT-23-5
U4: SN65HVD230; SOIC-8_3.9x4.9mm_P1.27mm

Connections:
+3.3V: C6.1, C7.2, J6.4, J7.3, R1.2, U1.5 (VOUT), U4.3 (VCC)
+5V: C1.1, C5.2, C8.2, C9.2, D2.1 (A1), J5.1, J12.3, J13.3, U1.1 (VIN), U1.3 (EN), U3.5 (VCC)
+48V: C2.2, C3.2, C4.2, D1.1 (K), J3.1, J4.4, J12.2, J13.2
/<NO NET>: C10.1, J5.3, Q2.1 (G), R1.1, R2.2, R4.1, R9.2
/CAN RX: J7.5, U4.4 (R)
/CAN TX: J7.4, U4.1 (D)
/CANH: J1.1, J2.1, J4.1, R5.2, U4.7 (CANH)
/CANL: J1.2, J2.2, J4.2, SW2.1 (A), U4.6 (CANL)
/CAN_SHLD: C11.2, J1.3, J2.3, R6.1, R10.2
/GPIO D0 (XIAO-ESP32-S3): J8.7, R3.1, U3.2
/GPIO D1 (XIAO-ESP32-S3): J8.6, R9.1
/GPIO D3 (XIAO-ESP32-S3): C12.1, J8.4, R7.2, R8.1
/GPIO D5# (XIAO-ESP32-S3): J8.2, R11.1
/GPIO D6 (XIAO-ESP32-S3): J6.2, J8.1
/GPIO D7 (XIAO-ESP32-S3): J6.3, J7.7
/MOSFET Out: D1.2 (A), Q2.2 (D), R7.1, TH1.2
/Treiber Out: R2.1, U3.4
GND: C1.2, C2.1, C3.1, C4.1, C5.1, C6.2, C7.1, C8.1, C9.1, C10.2, C11.1, C12.2, D2.2 (A2), D4.1 (K), J4.3, J5.2, J6.1, J7.2, J12.1, J13.1, Q2.3 (S), R3.2, R4.2, R6.2, R8.2, R10.1, U1.2 (GND), U3.1, U3.3 (GND), U4.2 (GND), U4.8 (Rs)
unnamed: D4.2 (A), R11.2
unnamed: J3.2, TH1.1
unnamed: J9.1, U2.14 (VBUS)
unnamed: J9.2, U2.13 (GND)
unnamed: J9.3, U2.12 (3V3)
unnamed: J9.4, U2.11 (GPIO9_A10_D10_MOSI)
unnamed: J9.5, U2.10 (GPIO8_A9_D9_MISO)
unnamed: J9.6, U2.9 (GPIO7_A8_D8_SCK)
unnamed: J9.7, U2.8 (GPIO44_D7_RX)
unnamed: J11.1, U2.7 (GPIO43_D6_TX)
unnamed: J11.2, U2.6 (GPIO6_A5_D5_SCL)
unnamed: J11.3, U2.5 (GPIO5_A4_D4_SDA)
unnamed: J11.4, U2.4 (GPIO4_A3_D3)
unnamed: J11.5, U2.3 (GPIO3_A2_D2)
unnamed: J11.6, U2.2 (GPIO2_A1_D1)
unnamed: J11.7, U2.1 (GPIO1_A0_D0)
unnamed: R5.1, SW2.2 (B)

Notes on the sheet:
XIAO-ESP32-S3 Microcontroller zum steuern 3.3V als Spannungsversorung J9 und J11 nur Platzhalter
Brake (Motor)
5V Voltage distribution
UART Ausgang für möglich Debuging
Canbus
Daisy Chain Roboterlink
Hallsensor (TLE4905L)
Anschluss für Bremse vom Motor Breme an (default) Bremse aus (10.5V kurz) Bremse aus halten (5V lang) PWM von 48V 48V fällt aus -> Bremse an GPIO D3 -> misst falls MOSFET durchgebrannt (Spannungsteiler) Spannungsteiler -> max 5V bei 80V Versorung (können nicht anliegen) C12 -> "lässt" kein PVM durc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
Eingang und Ausgang von 48V, 5V und GND 100u (ca. 100V fest) Kondensator zum Puffern von Energie -> kurzzeitig
Status LED
Canubs Ein - und Ausgang J4 Ausgang zu Motor (48V, GND, CANH und CANL) Canbus vom ESP32-S3 Shilding mit 1M Ohm und 100nF (und Kabelanschluss) Kann auf GND überbrückt werden mit DNP 120 Ohm -> aktivierbarer Abschlusswiderstand
Power Connectors
5V zu 3.3V Logik D2 als Schutz Überspannung Imax = 600mA
UART Debug
LED für Statusanzeige
XIOA ESP32 S3
Anschluss für den Hallsensor (TLE4905L) Zuständig für Homing 5V, GND und Ausgang 1k Widerstand -> Strombegrenzung (Schutz) 4,7k Widerstand -> Pullup zu 3,3V

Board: 4 copper layers, 42 parts (0 on the bottom side), 20 nets, no tracks yet.

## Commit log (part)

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2026-05-02 Initial commit: add src and doku folders
2026-05-02 Add README.md and .gitignore
2026-05-02 Remove Python package installation and slider_control.py from CMakeLists.txt
2026-05-02 Add CAN communication and motor driver implementation for r0192
    - Created CMakeLists.txt for building the r0192_canbus package.
    - Implemented CanCommunication class for CAN bus communication.
    - Added GDS34Driver and GDS68Driver classes for controlling respective motor controllers.
    - Defined AxisState message for reporting motor state.
    - Created MotorCommand service for sending commands to motor drivers.
    - Implemented can_service_node to handle service requests and publish motor states.
2026-05-02 Add instructions to start robot launch frequency in README.md
2026-05-02 Fix install order of directories in CMakeLists.txt for r0192_controller and r0192_moveit
2026-05-02 Remove software installation and development sections
    Removed software installation instructions and development guidelines from README.
2026-05-05 Implement RS05Driver class and its methods for CAN communication
2026-05-07 Refactor RS05Driver class: implement CAN communication methods and update feedback processing
2026-05-08 Refactor r0192 project: Remove obsolete files and implement new hardware interface
    - Deleted `can_service_node.cpp` and associated service files as they are no longer needed.
    - Removed `MotorCommand.srv` and related message definitions from `r0192_msgs`.
    - Eliminated `r0192_controller` interface files and related implementations.
    - Removed `angle_conversion` utility and its associated files from `r0192_utils`.
    - Introduced new `R0192SystemHardware` interface in `r0192_hardware` to manage hardware communication and control.
    - Implemented CAN communication and driver management within the new hardware interface.
2026-05-10 Refactor robotic arm configuration: update controller parameters and add new hardware interface files
2026-05-10 Refactor RS05Driver and GDS68Driver integration, enhance CAN communication handling, and update MoveIt configuration
    - Implemented placeholder return values for unimplemented functions in RS05Driver.
    - Added thread safety for feedback frame processing in RS05Driver.
    - Updated CMakeLists.txt to remove unnecessary dependencies and streamline build process.
    - Increased update rate in r0192_controllers.yaml for improved control responsiveness.
    - Adjusted joint limits in URDF files for gripper joints to ensure correct operation.
    - Enhanced r0192_ros2_control.xacro for better simulation and real robot handling.
2026-05-12 Enhance GDS68Driver and configuration: add Set_Linear_Count method, enable open loop control, and adjust MoveIt execution timeout margins
2026-05-12 feat: switch axis 1 control mode from MIT_Control to internal position control to mitigate drift
2026-05-12 refactor: disable automatic homing sequence, increase controller update rate, and enable closed-loop trajectory control with relaxed tolerances
2026-05-12 chore: update controller update rate to 100Hz, disable encoder estimates, and add RS05 manual documentation
2026-05-12 refactor: replace software-based offset homing with hardware-level zero setting and remove unused diagnostic logging.
2026-05-12 feat: revert joint_1 command to MIT_Control for improved hardware synchronization
2026-05-18 docs: update README to enhance clarity on project features and system architecture
2026-05-20 feat: add probePresent method to GDS68Driver and RS05Driver for hardware detection
2026-05-20 feat: enhance sendFrame method to support forced extended frame transmission
2026-05-21 feat: add launch arguments for RViz and rosbridge WebSocket support in real_robot and moveit launch files
2026-05-21 feat: migrate from rosbridge_server to foxglove_bridge for native Foxglove support
2026-05-25 feat: add initial implementation of homing sequence code for microcontroller
2026-05-25 feat: update homing sequence to use TLE4905L Hall sensors and adjust CAN bitrate to 1 Mbit/s
2026-05-25 Refactor code structure for improved readability and maintainability
2026-05-27 feat: implement Arduino-based homing sequence with TLE4905L sensors and ROS service integration
2026-05-31 Add RViz operator panel and motor control functionality
    - Introduced an OperatorPanel for RViz to control the R0192 arm, allowing users to trigger homing and enable/disable motors via services.
    - Implemented service clients for /homing (std_srvs/Trigger) and /robot_enable (std_srvs/SetBool) in the OperatorPanel.
    - Added safety checks to ensure motors are only activated when encoders are within URDF limits.
    - Updated motor control logic to handle enabling/disabling motors without affecting the main control loop.
    - Modified homing parameters for improved performance.
    - Enhanced RViz configuration to include the new OperatorPanel and adjusted visualization settings.
2026-05-31 feat: add auto-reset functionality for RViz displays after homing
2026-06-05 Add JogPanel for teach-pendant style jogging and integrate MoveIt Servo
    - Introduced a new JogPanel in r0192_rviz_plugins for controlling the R0192 arm via teach-pendant style jogging.
    - Implemented joint and Cartesian jogging modes with corresponding buttons and a speed slider.
    - Integrated the JogPanel with MoveIt Servo for real-time control, allowing for smooth operation while maintaining safety.
    - Updated launch files to include the new servo_node for handling jogging commands.
    - Modified URDF to add a TCP link for tool frame reference.
    - Enhanced the r0192_hardware_interface to ensure motors remain disabled after activation until explicitly enabled by the operator.
2026-06-05 Refactor URDF and RViz configurations for real-scale implementation
    - Updated joint limits for joint_7 in CLAUDE.md and URDF to reflect real dimensions (0.0025 m).
    - Adjusted URDF geometry scaling to 1:1 with real measurements, modifying mesh scales and joint origins accordingly.
    - Revised MoveIt configuration to restore default singularity thresholds, now suitable for real-scale links.
    - Enhanced RViz configuration for improved visualization, including adjustments to grid size and view settings.
    - Implemented live readout for joint angles and TCP pose in jog_panel, utilizing TF for real-time updates.
    - Added necessary dependencies for sensor_msgs and tf2 in CMakeLists.txt and package.xml.
2026-06-06 feat: merge OperatorPanel functionality into JogPanel and update RViz configuration
2026-06-06 Implement feature X to enhance user experience and optimize performance
2026-06-06 refactor: update GDS68 feedback handling to use Encoder_Estimates for position and velocity
2026-06-06 feat: implement feedback polling for RS05 in disabled state to track position and velocity
2026-06-06 feat: Implement robot state manager and interfaces for R0192 arm
    - Added a new `robot_state_manager` node to manage the state transitions of the R0192 arm.
    - Introduced five states: DISABLED, HOLD, JOG, MOVEIT, and HOMING, with appropriate service calls for transitions.
    - Created custom ROS 2 interfaces in `r0192_interfaces` package, including `RobotState.msg` and `SetRobotState.srv`.
    - Updated `jog_panel` to interact with the new state manager, replacing previous service calls with state transitions.
    - Added emergency stop and reset functionalities to handle faults and state management.
    - Enhanced UI feedback based on the current robot state, ensuring clear communication of status to the us
2026-06-11 feat(rviz): update moveit configuration for improved layout and visibility
2026-06-12 feat: implement phase 6 features — add move_l functionality, point visualization, and demo program
2026-06-13 feat: Enhance program execution with blending and dry run options
    - Added support for blending through consecutive moves using the 'c_dis' parameter in the program loader.
    - Introduced new step types: 'ptp', 'lin', and 'circ' with appropriate validation and error handling.
    - Implemented UI elements in the program panel for enabling blending and dry run modes.
    - Created demo YAML files to showcase the new blending and circular motion capabilities.
    - Added comprehensive unit tests for the program loader, covering various scenarios including point validation and program execution.
2026-06-13 feat: Update program execution model with new KRL vocabulary and dry run mode
2026-06-19 docs: Update README with hardware status and actuator details
2026-06-19 docs: Remove "hochpräziser" from robot description and add umbilical connection details
2026-06-19 docs: Ergänze Verkabelungsdetails und Materialkosten im README
2026-06-25 docs: Update power supply details in README with new model and specifications
2026-06-27 feat: Füge Daisy-Chain-Board-Dokumentation hinzu

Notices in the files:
README.md:
License: MIT
Dieses Projekt ist unter der MIT License lizenziert - siehe die [LICENSE](LICENSE) Datei für Details.
